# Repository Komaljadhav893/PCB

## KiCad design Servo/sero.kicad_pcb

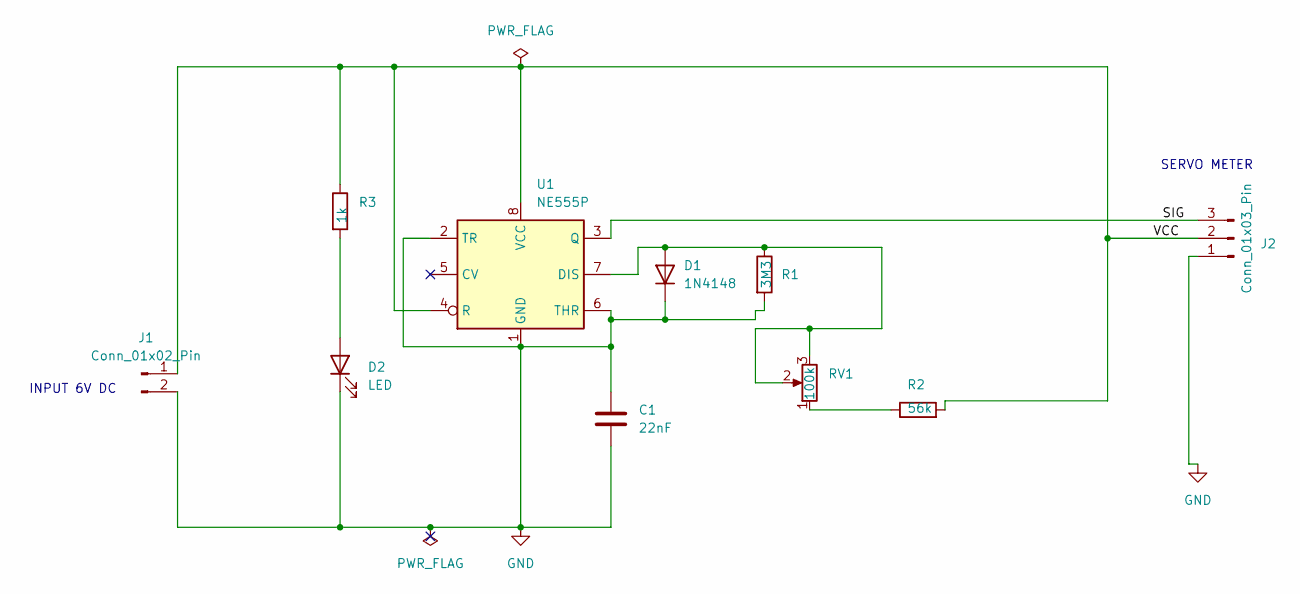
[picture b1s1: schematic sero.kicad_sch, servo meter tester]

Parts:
C1: 22nF
D1: 1N4148; D_DO-35_SOD27_P7.62mm_Horizontal
D2: LED
J1: Conn_01x02_Pin
J2: Conn_01x03_Pin
R1: 3M3
R2: 56k
R3: 1k
RV1: 100k
U1: NE555P; DIP-8_W7.62mm

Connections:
/SIG: J2.3, U1.3 (Q)
/VCC: J1.1, J2.2, R2.2, R3.1, U1.4 (R), U1.8 (VCC)
GND: C1.1, C1.2, D1.1 (K), D2.1 (K), J1.2, J2.1, R1.2, U1.1 (GND), U1.2 (TR), U1.6 (THR)
unnamed: D1.2 (A), R1.1, RV1.2, RV1.3, U1.7 (DIS)
unnamed: D2.2 (A), R3.2
unnamed: R2.1, RV1.1

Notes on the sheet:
SERVO METER
INPUT 6V DC

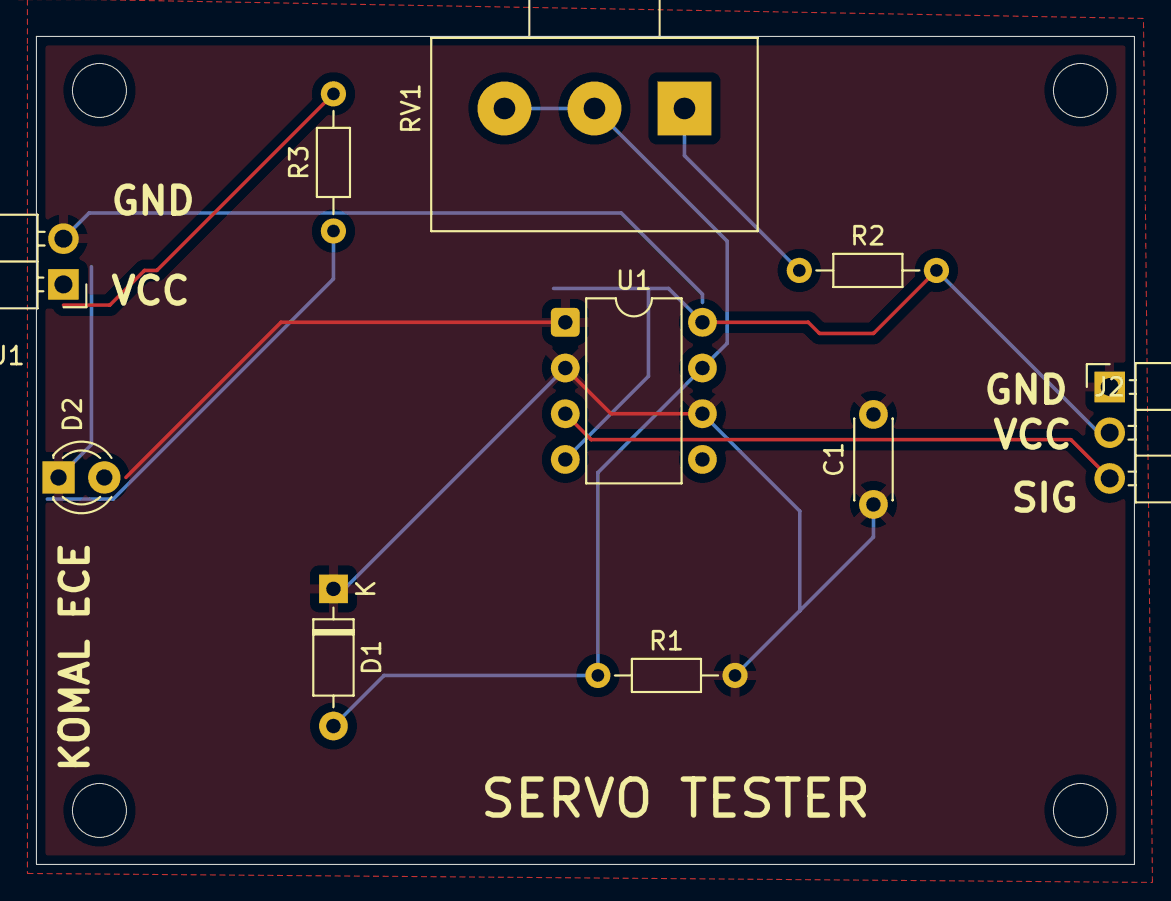
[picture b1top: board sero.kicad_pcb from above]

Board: 2 copper layers, 61.0 x 46.0 mm, 10 parts (0 on the bottom side), 6 nets.

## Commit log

2025-03-13 Create waste
2025-03-13 📌 Project Overview:
2025-03-16 Create overview
